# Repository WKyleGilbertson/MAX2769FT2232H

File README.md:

"# MAX2769FT2232H" 
This design was created to provide a hands-on platform for exploring GPS signal processing. When assembled according to the default configuration, and flashed with the appropriate FT_PROG file (L1IFStream.xml), the card should stream GPS IF data out of the USB port. The jumper configuration is selected among three different settings. It is recommended to start with the default configuration before configuring for software-controlled configuration.

This design was created because this one: https://pdfserv.maximintegrated.com/en/an/AN4275.pdf was never made available.

Fully assembled and tested version of this card may be obtained here: https://www.navstargps.us/

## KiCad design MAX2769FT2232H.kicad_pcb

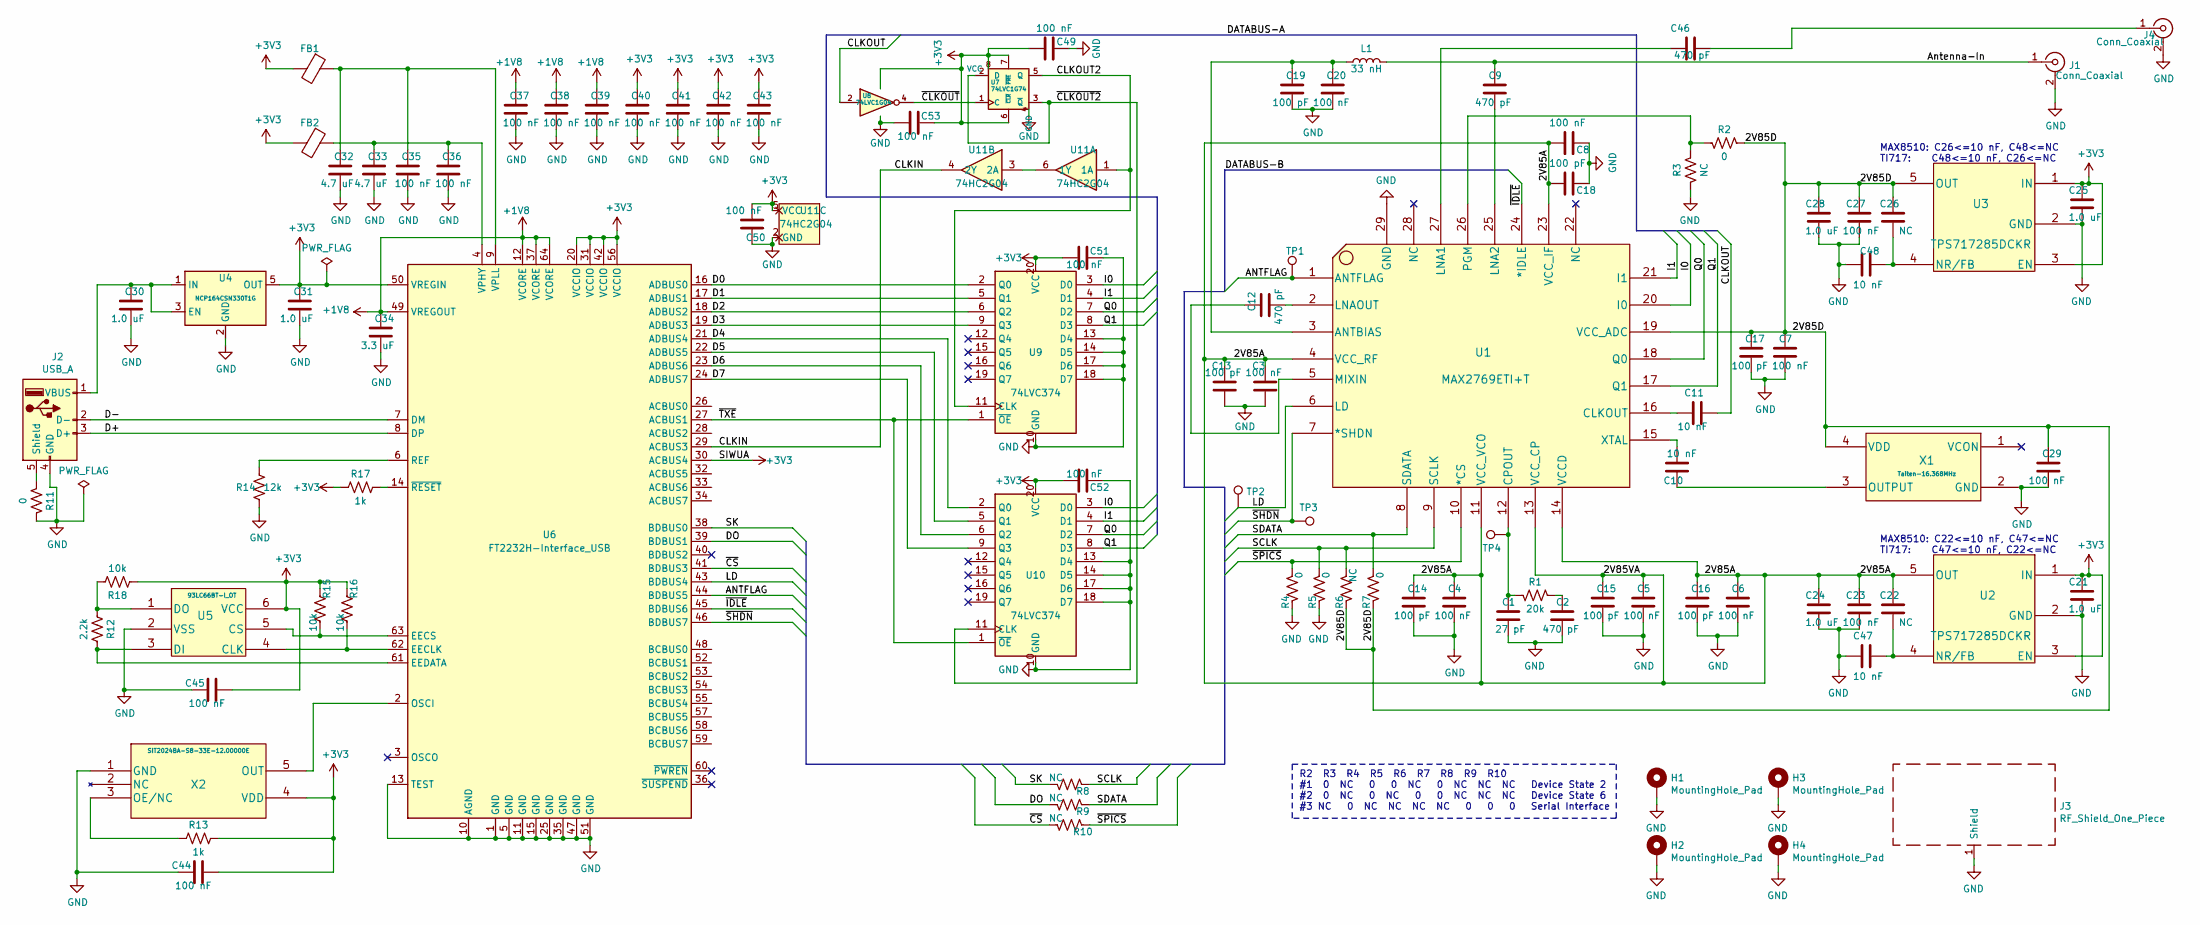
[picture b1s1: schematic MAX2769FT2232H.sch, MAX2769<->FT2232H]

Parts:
C1: 27 pF; C_0402_1005Metric; Digi-Key 490-12651-1-ND
C2, C9, C12, C46: 470 pF; C_0402_1005Metric; Digi-Key 490-6242-1-ND
C3, C4, C5, C6, C7, C8, C20, C23, C27, C29, C35, C36, C37, C38, C39, C40, C41, C42, C43, C44, C45, C49, C50, C51, C52, C53: 100 nF; C_0402_1005Metric; Digi-Key 490-6328-1-ND
C10, C11, C47, C48: 10 nF; C_0402_1005Metric; Digi-Key 399-7759-1-ND
C13, C14, C15, C16, C17, C18, C19: 100 pF; C_0402_1005Metric; Digi-Key 399-3194-1-ND
C21, C24, C25, C28, C30, C31: 1.0 uF; C_0402_1005Metric; Digi-Key 490-12233-1-ND
C22, C26: NC; C_0402_1005Metric; Digi-Key 399-7759-1-ND
C32, C33: 4.7 uF; C_0805_2012Metric; Digi-Key 399-15725-1-ND
C34: 3.3 uF; C_0805_2012Metric; Digi-Key 490-13309-1-ND
FB1, FB2: Ferrite_Bead; L_0805_2012Metric; Digi-Key 490-1041-1-ND
H1, H2, H3, H4: MountingHole_Pad; MountingHole_2.2mm_M2_Pad_Via
J1: Conn_Coaxial; SMA_Amphenol_132203-12_Horizontal; Digi-Key ACX1232-ND
J2: USB_A; USB_A_CNCTech_1001-011-01101_Horizontal; Digi-Key WM3983CT-ND
J3: RF_Shield_One_Piece; Laird_Technologies_BMI-S-103_26.21x26.21mm; Digi-Key 903-1008-1-ND
J4: Conn_Coaxial; MMCX_Molex_73415-1471_Vertical; Digi-Key ARF1904-ND
L1: 33 nH; L_0402_1005Metric; Digi-Key 490-2629-1-ND
R1: 20k; R_0603_1608Metric; Digi-Key 2019-RK73H1JTTD2002FCT-ND
R2, R4, R5, R7, R11: 0; R_0603_1608Metric; Digi-Key 2019-RK73Z1JTTDCT-ND
R3, R6, R8, R9, R10: NC; R_0603_1608Metric; Digi-Key 2019-RK73Z1JTTDCT-ND
R12: 2.2k; R_0603_1608Metric; Digi-Key 2019-RK73H1JTTD2201FCT-ND
R13, R17: 1k; R_0603_1608Metric; Digi-Key 2019-RK73H1JTTD1001FCT-ND
R14: 12k; R_0603_1608Metric; Digi-Key 2019-RK73H1JTTD1202FCT-ND
R15, R16, R18: 10k; R_0603_1608Metric; Digi-Key 2019-RK73H1JTTD1002FCT-ND
TP1, TP2, TP3, TP4: TestPoint; TestPoint_Pad_D1.0mm
U1: MAX2769ETI+T; MAX2769ETI&plus_T; Digi-Key MAX2769BETI/V+-ND
U2, U3: TPS717285DCKR; Digi-Key 296-19649-1-ND
U4: NCP164CSN330T1G; TSOT-23-5; Digi-Key 488-NCP164CSN330T1GCT-ND
U5: 93LC66BT-I_OT; 93LC66BT-I&slash_OT; Digi-Key 93LC66BT-I/OTCT-ND
U6: FT2232H-Interface_USB; LQFP-64_10x10mm_P0.5mm; Digi-Key 768-1024-1-ND
U7: 74LVC1G74; SOT-833-1; Digi-Key 1727-3558-1-ND
U8: 74LVC1G04; SOT-353_SC-70-5; Digi-Key 1727-2871-1-ND
U9, U10: 74LVC374; TSSOP-20_4.4x6.5mm_P0.65mm; Digi-Key 1727-4034-1-ND
U11: 74HC2G04; SOT-363_SC-70-6
X1: Taiten-16.368MHz; TXETCDSANF-16.368000; Digi-Key 1664-1271-1-ND
X2: SIT2024BA-S8-33E-12.00000E; SIT2024BA-S8-33E-8.000000E; Digi-Key 1473-SIT2024BA-S8-33E-12.000000G-ND

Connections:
+1V8: C34.1, C37.1, C38.1, C39.1, U6.12 (VCORE), U6.37 (VCORE), U6.49 (VREGOUT), U6.64 (VCORE)
+3V3: C21.1, C25.1, C31.1, C40.1, C41.1, C42.1, C43.1, C44.2, C45.2, C49.2, C50.2, C51.1, C52.1, C53.2, FB1.2, FB2.2, R13.1, R15.2, R16.2, R17.2, R18.2, U2.1 (IN), U2.3 (EN), U3.1 (IN), U3.3 (EN), U4.5 (OUT), U5.6 (VCC), U6.20 (VCCIO), U6.30 (ACBUS4), U6.31 (VCCIO), U6.42 (VCCIO), U6.50 (VREGIN), U6.56 (VCCIO), U7.6 (~CLR), U7.7 (~PRE), U7.8 (VCC), U8.5 (VCC), U9.20 (VCC), U10.20 (VCC), U11.5 (VCC), X2.4 (VDD)
/2V85A: C3.1, C4.1, C5.1, C6.1, C8.2, C13.1, C14.1, C15.1, C16.1, C18.2, C22.1, C23.1, C24.1, U1.4 (VCC_RF), U1.11 (VCC_VCO), U1.13 (VCC_CP), U1.14 (VCCD), U1.23 (VCC_IF), U2.5 (OUT)
/2V85D: C7.1, C17.1, C26.1, C27.1, C28.1, C29.1, R2.2, R6.2, R7.2, U1.19 (VCC_ADC), U3.5 (OUT), X1.4 (VDD)
/ANTFLAG: TP1.1, U1.1 (ANTFLAG), U6.44 (BDBUS5)
/Antenna-In: C9.1, J1.1 (In), L1.2
/CLKIN: U6.29 (ACBUS3), U11.4 (2Y)
/CLKOUT: C11.1, U8.2
/CLKOUT2: U7.5 (Q), U9.11 (CLK), U11.1 (1A)
/D0: U6.16 (ADBUS0), U9.2 (Q0)
/D1: U6.17 (ADBUS1), U9.5 (Q1)
/D2: U6.18 (ADBUS2), U9.6 (Q2)
/D3: U6.19 (ADBUS3), U9.9 (Q3)
/D4: U6.21 (ADBUS4), U10.2 (Q0)
/D5: U6.22 (ADBUS5), U10.5 (Q1)
/D6: U6.23 (ADBUS6), U10.6 (Q2)
/D7: U6.24 (ADBUS7), U10.9 (Q3)
/D+: J2.3 (D+), U6.8 (DP)
/D-: J2.2 (D-), U6.7 (DM)
/DO: R9.2, U6.39 (BDBUS1)
/I0: U1.20 (I0), U9.3 (D0), U10.3 (D0)
/I1: U1.21 (I1), U9.4 (D1), U10.4 (D1)
/LD: TP2.1, U1.6 (LD), U6.43 (BDBUS4)
/Q0: U1.18 (Q0), U9.7 (D2), U10.7 (D2)
/Q1: U1.17 (Q1), U9.8 (D3), U10.8 (D3)
/SCLK: R5.2, R6.1, R8.1, U1.9 (SCLK)
/SDATA: R7.1, R9.1, U1.8 (SDATA)
/SK: R8.2, U6.38 (BDBUS0)
/~CLKOUT: U7.1 (C), U8.4
/~CLKOUT2: U7.2 (D), U7.3 (~Q), U10.11 (CLK)
/~CS: R10.2, U6.41 (BDBUS3)
/~IDLE: U1.24 (*IDLE), U6.45 (BDBUS6)
/~SHDN: TP3.1, U1.7 (*SHDN), U6.46 (BDBUS7)
/~SPICS: R4.2, R10.1, U1.10 (*CS)
/~TXE: U6.27 (ACBUS1), U9.1 (~OE), U10.1 (~OE)
GND: C1.2, C2.2, C3.2, C4.2, C5.2, C6.2, C7.2, C8.1, C13.2, C14.2, C15.2, C16.2, C17.2, C18.1, C19.2, C20.2, C21.2, C23.2, C24.2, C25.2, C27.2, C28.2, C29.2, C30.2, C31.2, C32.2, C33.2, C34.2, C35.2, C36.2, C37.2, C38.2, C39.2, C40.2, C41.2, C42.2, C43.2, C44.1, C45.1, C47.2, C48.2, C49.1, C50.1, C51.2, C52.2, C53.1, H1.1, H2.1, H3.1, H4.1, J1.2 (Ext), J2.4 (GND), J3.1, J4.2 (Ext), R3.1, R4.1, R5.1, R11.2, R14.2, U1.29 (GND), U2.2 (GND), U3.2 (GND), U4.2 (GND), U5.2 (VSS), U6.1 (GND), U6.5 (GND), U6.10 (AGND), U6.11 (GND), U6.13 (TEST), U6.15 (GND), U6.25 (GND), U6.35 (GND), U6.47 (GND), U6.51 (GND), U7.4 (GND), U8.3 (GND), U9.10 (GND), U9.13 (D4), U9.14 (D5), U9.17 (D6), U9.18 (D7), U10.10 (GND), U10.13 (D4), U10.14 (D5), U10.17 (D6), U10.18 (D7), U11.2 (GND), X1.2 (GND), X2.1 (GND)
unnamed: C1.1, R1.1, TP4.1, U1.12 (CPOUT)
unnamed: C2.1, R1.2
unnamed: C9.2, U1.25 (LNA2)
unnamed: C10.1, X1.3 (OUTPUT)
unnamed: C10.2, U1.15 (XTAL)
unnamed: C11.2, U1.16 (CLKOUT)
unnamed: C12.1, U1.5 (MIXIN)
unnamed: C12.2, U1.2 (LNAOUT)
unnamed: C19.1, C20.1, L1.1, U1.3 (ANTBIAS)
unnamed: C22.2, C47.1, U2.4 (NR/FB)
unnamed: C26.2, C48.1, U3.4 (NR/FB)
unnamed: C30.1, J2.1 (VBUS), U4.1 (IN), U4.3 (EN)
unnamed: C32.1, C35.1, FB1.1, U6.9 (VPLL)
unnamed: C33.1, C36.1, FB2.1, U6.4 (VPHY)
unnamed: C46.1, U1.27 (LNA1)
unnamed: C46.2, J4.1 (In)
unnamed: J2.5 (Shield), R11.1
unnamed: R2.1, R3.2, U1.26 (PGM)
unnamed: R12.1, U5.3 (DI), U6.61 (EEDATA)
unnamed: R12.2, R18.1, U5.1 (DO)
unnamed: R13.2, X2.3 (OE/NC)
unnamed: R14.1, U6.6 (REF)
unnamed: R15.1, U5.5 (CS), U6.63 (EECS)
unnamed: R16.1, U5.4 (CLK), U6.62 (EECLK)
unnamed: R17.1, U6.14 (~RESET)
unnamed: U6.2 (OSCI), X2.5 (OUT)
unnamed: U11.3 (2A), U11.6 (1Y)

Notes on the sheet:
R2 R3 R4 R5 R6 R7 R8 R9 R10 #1 0 NC 0 0 NC 0 NC NC NC Device State 2 #2 0 NC 0 NC 0 0 NC NC NC Device State 6 #3 NC 0 NC NC NC NC 0 0 0 Serial Interface
MAX8510: C26<=10 nF, C48<=NC TI717: C48<=10 nF, C26<=NC
MAX8510: C22<=10 nF, C47<=NC TI717: C47<=10 nF, C22<=NC

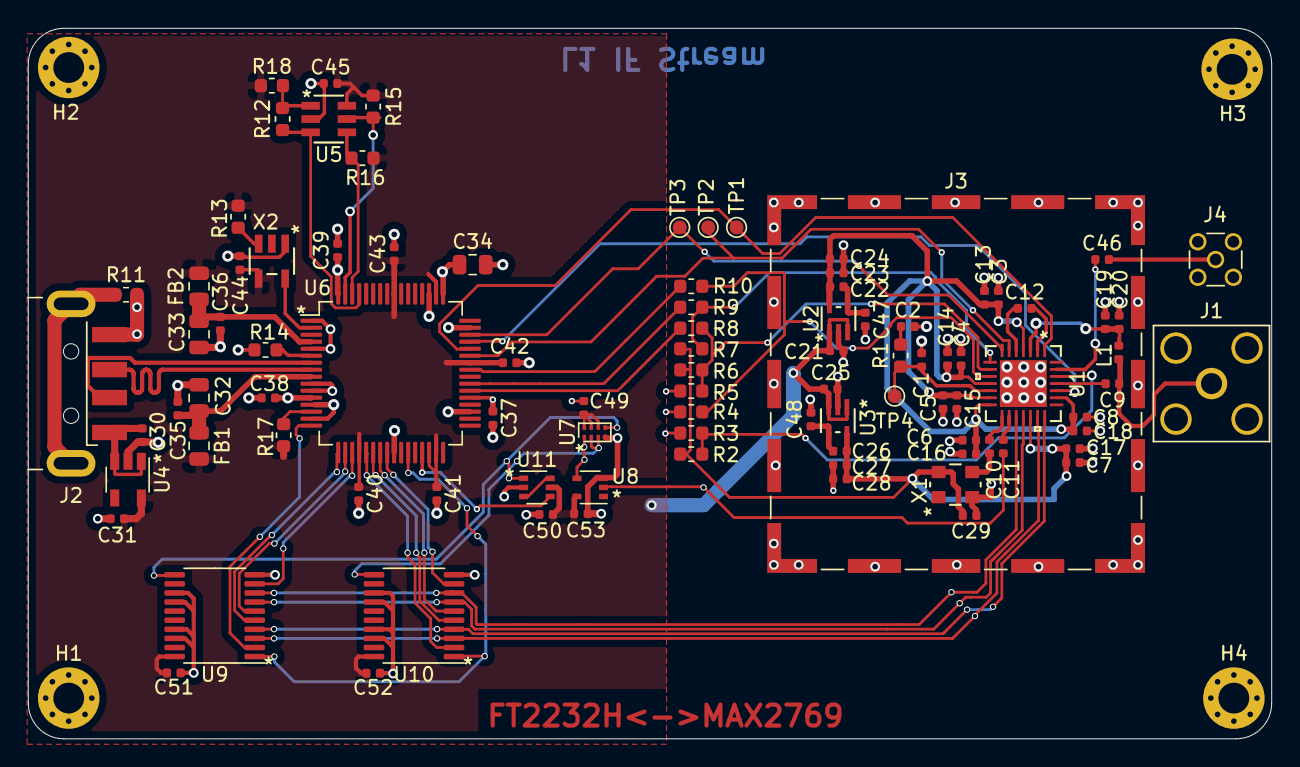
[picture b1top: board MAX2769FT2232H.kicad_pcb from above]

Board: 4 copper layers, 88.9 x 50.8 mm, 99 parts (0 on the bottom side), 63 nets.

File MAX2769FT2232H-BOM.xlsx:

Item | Qty | Reference(s) | Value | LibPart | Footprint | Datasheet | Description | Digi-Key
1 | 1 | C1 | 27 pF | MAX2769FT2232H:C | MAX2769FT2232H:C_0402_1005Metric | ~ | CAP CER 27PF 50V C0G/NP0 0402 5% | 490-12651-1-ND
2 | 4 | C2, C9, C12, C46 | 470 pF | MAX2769FT2232H:C | MAX2769FT2232H:C_0402_1005Metric | ~ | CAP CER 470PF 50V C0G/NP0 0402 10% | 490-6242-1-ND
3 | 26 | C3, C4, C5, C6, C7, C8, C20, C23, C27, C29, C35, C36, C37, C38, C39, C40, C41, 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 | 100 nF | MAX2769FT2232H:C | MAX2769FT2232H:C_0402_1005Metric | ~ | CAP CER 0.1UF 16V X7R 0402 10% | 490-6328-1-ND
4 | 4 | C10, C11, C47, C48 | 10 nF | MAX2769FT2232H:C | MAX2769FT2232H:C_0402_1005Metric | ~ | CAP CER 10000PF 10V X7R 0402 10% | 399-7759-1-ND
5 | 7 | C13, C14, C15, C16, C17, C18, C19 | 100 pF | MAX2769FT2232H:C | MAX2769FT2232H:C_0402_1005Metric | ~ | CAP CER 100PF 50V C0G/NP0 0402 5% | 399-3194-1-ND
6 | 6 | C21, C24, C25, C28, C30, C31 | 1.0 uF | MAX2769FT2232H:C | MAX2769FT2232H:C_0402_1005Metric | ~ | CAP CER 1UF 6.3V X6S 0402 | 490-12233-1-ND
7 | 2 | C22, C26 | NC | MAX2769FT2232H:C | MAX2769FT2232H:C_0402_1005Metric | ~ | CAP CER 10000PF 10V X7R 0402 | 399-7759-1-ND
8 | 2 | C32, C33 | 4.7 uF | MAX2769FT2232H:C | MAX2769FT2232H:C_0805_2012Metric | ~ | CAP CER 4.7UF 6.3V X7R 0805 | 399-15725-1-ND
9 | 1 | C34 | 3.3 uF | MAX2769FT2232H:C | MAX2769FT2232H:C_0805_2012Metric | ~ | CAP CER 3.3UF 16V X7R 0805 | 490-13309-1-ND
10 | 2 | FB1, FB2 | Ferrite_Bead | MAX2769FT2232H:Ferrite_Bead | MAX2769FT2232H:L_0805_2012Metric | ~ | FERRITE BEAD 1 KOHM 0805 1LN | 490-1041-1-ND
12 | 1 | J1 | Conn_Coaxial | MAX2769FT2232H:Conn_Coaxial | MAX2769FT2232H:SMA_Amphenol_132203-12_Horizontal | ~ | CONN SMA JACK R/A 50 OHM PCB | ACX1232-ND
13 | 1 | J2 | USB_A | MAX2769FT2232H:USB_A | MAX2769FT2232H:USB_A_CNCTech_1001-011-01101_Horizontal | ~ | CONN PLUG USB2.0 TYPEA 4P SMD RA | WM3983CT-ND
14 | 1 | J3 | RF_Shield_One_Piece | MAX2769FT2232H:RF_Shield_One_Piece | MAX2769FT2232H:Laird_Technologies_BMI-S-103_26.21x26.21mm | ~ | RF SHIELD 1.032"X1.032" SLDR 1PC | 903-1008-1-ND
15 | 1 | J4 | Conn_Coaxial | MAX2769FT2232H:Conn_Coaxial | MAX2769FT2232H:MMCX_Molex_73415-1471_Vertical | ~ | CONN MMCX JACK STR 50 OHM PCB | ARF1904-ND
16 | 1 | L1 | 33 nH | MAX2769FT2232H:L | MAX2769FT2232H:L_0402_1005Metric | ~ | FIXED IND 33NH 350MA 580 MOHM | 490-2629-1-ND
17 | 1 | R1 | 20k | MAX2769FT2232H:R_US | MAX2769FT2232H:R_0603_1608Metric | ~ | RES 20K OHM 1% 1/10W 0603 | 2019-RK73H1JTTD2002FCT-ND
18 | 5 | R2, R4, R5, R7, R11 | 0 | MAX2769FT2232H:R_US | MAX2769FT2232H:R_0603_1608Metric | ~ | RES 0 OHM JUMPER 0603 | 2019-RK73Z1JTTDCT-ND
19 | 5 | R3, R6, R8, R9, R10 | NC | MAX2769FT2232H:R_US | MAX2769FT2232H:R_0603_1608Metric | ~ | RES 0 OHM JUMPER 0603 | 2019-RK73Z1JTTDCT-ND
20 | 1 | R12 | 2.2k | MAX2769FT2232H:R_US | MAX2769FT2232H:R_0603_1608Metric | ~ | RES 2.2K OHM 1% 1/10W 0603 | 2019-RK73H1JTTD2201FCT-ND
21 | 2 | R13, R17 | 1k | MAX2769FT2232H:R_US | MAX2769FT2232H:R_0603_1608Metric | ~ | RES 1K OHM 1% 1/8W 0603 | 2019-RK73H1JTTD1001FCT-ND
22 | 1 | R14 | 12k | MAX2769FT2232H:R_US | MAX2769FT2232H:R_0603_1608Metric | ~ | RES 12K OHM 1% 1/10W 0603 | 2019-RK73H1JTTD1202FCT-ND
23 | 3 | R15, R16, R18 | 10k | MAX2769FT2232H:R_US | MAX2769FT2232H:R_0603_1608Metric | ~ | RES 10K OHM 1% 1/10W 0603 | 2019-RK73H1JTTD1002FCT-ND
24 | 1 | U1 | MAX2769ETI+T | MAX2769FT2232H:MAX2769ETI+T | MAX2769FT2232H:MAX2769ETI&plus_T |  | RF RX GNSS 1575.42MHZ 28TQFN | MAX2769BETI/V+-ND
25 | 2 | U2, U3 | TPS717285DCKR | MAX2769FT2232H:TPS717285DCKR | MAX2769FT2232H:TPS717285DCKR |  | IC REG LINEAR 2.85V 150MA SC70-5 | 296-19649-1-ND
26 | 1 | U4 | NCP164CSN330T1G | MAX2769FT2232H:NCP164CSN330T1G | MAX2769FT2232H:TSOT-23-5 | https://www.onsemi.com/pub/Collateral/NCP164C-D.PDF | LDO 300 MA AD 3.3V, ULTRA | 488-NCP164CSN330T1GCT-ND
27 | 1 | U5 | 93LC66BT-I_OT | MAX2769FT2232H:93LC66BT-I_OT | MAX2769FT2232H:93LC66BT-I&slash_OT |  | IC EEPROM 4K SPI 2MHZ SOT23-6 | 93LC66BT-I/OTCT-ND
28 | 1 | U6 | FT2232H-Interface_USB | MAX2769FT2232H:FT2232H-Interface_USB | MAX2769FT2232H:LQFP-64_10x10mm_P0.5mm |  | IC USB HS DUAL UART/FIFO 64-LQFP | 768-1024-1-ND
29 | 1 | U7 | 74LVC1G74 | MAX2769FT2232H:74LVC1G74 | MAX2769FT2232H:SOT-833-1 | https://assets.nexperia.com/documents/data-sheet/74LVC1G74.pdf | IC FF D-TYPE SNGL 1BIT 8XSON | 1727-3558-1-ND
30 | 1 | U8 | 74LVC1G04 | MAX2769FT2232H:74LVC1G04 | MAX2769FT2232H:SOT-353_SC-70-5 | https://assets.nexperia.com/documents/data-sheet/74LVC1G04.pdf | IC INVERTER 1CH 1-INP 5TSSOP | 1727-2871-1-ND
31 | 2 | U9, U10 | 74LVC374 | MAX2769FT2232H:74LVC374 | MAX2769FT2232H:TSSOP-20_4.4x6.5mm_P0.65mm | https://assets.nexperia.com/documents/data-sheet/74LVC374A.pdf | IC FF D-TYPE SNGL 8BIT 20TSSOP | 1727-4034-1-ND
32 | 1 | U11 | 74HC2G04 | MAX2769FT2232H:74HC2G04 | MAX2769FT2232H:SOT-363_SC-70-6 | https://assets.nexperia.com/documents/data-sheet/74HC_HCT2G04.pdf | IC INVERTER 2CH 2-INP 6TSSOP | 1727-6045-1-ND
33 | 1 | X1 | Taiten-16.368MHz | MAX2769FT2232H:Taiten-16.368MHz | MAX2769FT2232H:TXETCDSANF-16.368000 |  | XTAL OSC TCXO 16.3680MHZ SNWV | 1664-1271-1-ND
34 | 1 | X2 | SIT2024BA-S8-33E-12.00000E | MAX2769FT2232H:SIT2024BA-S8-33E-12.00000E | MAX2769FT2232H:SIT2024BA-S8-33E-8.000000E |  | MEMS OSC XO 12.0000MHZ LVCMOS LV | 1473-SIT2024BA-S8-33E-12.000000G-ND

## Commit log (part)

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2021-04-15 Adding Design Files
2021-04-17 Setup PCB new to only show assembly view
2021-04-19 First Pass BOM
2021-04-19 remove extra files
2021-04-29 Adding FT2232H Configfile
2022-06-12 Added Note concerning voltage regulator caps
2022-06-12 Voltage Regulator Circuit
    Added note to schematic regarding capacitors used with different voltage regulators
2022-06-12 Removed pdfs
2022-06-12 Added pdf of schematic
2022-06-12 Added Assembly Drawing
2022-06-12 Added Flash Instructions
2023-06-26 Missed an h in flash
2023-06-26 Added board image
2023-06-26 Modified image
2023-06-28 Added STEP files
2024-02-01 Update README.md
    Added reference to MAXIM's original USB GPS.
2024-02-01 Update README.md
    Added reference to online store
2024-06-21 Adding CERN License

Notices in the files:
MAX2769FT2232H.kicad_pcb:
License: CC BY 4.0
MAX2769FT2232H.sch:
creativecommons.org/licenses/by/4.0
parts and their libraries:
Copyright 2016 Accelerated Designs. All rights reserved.
